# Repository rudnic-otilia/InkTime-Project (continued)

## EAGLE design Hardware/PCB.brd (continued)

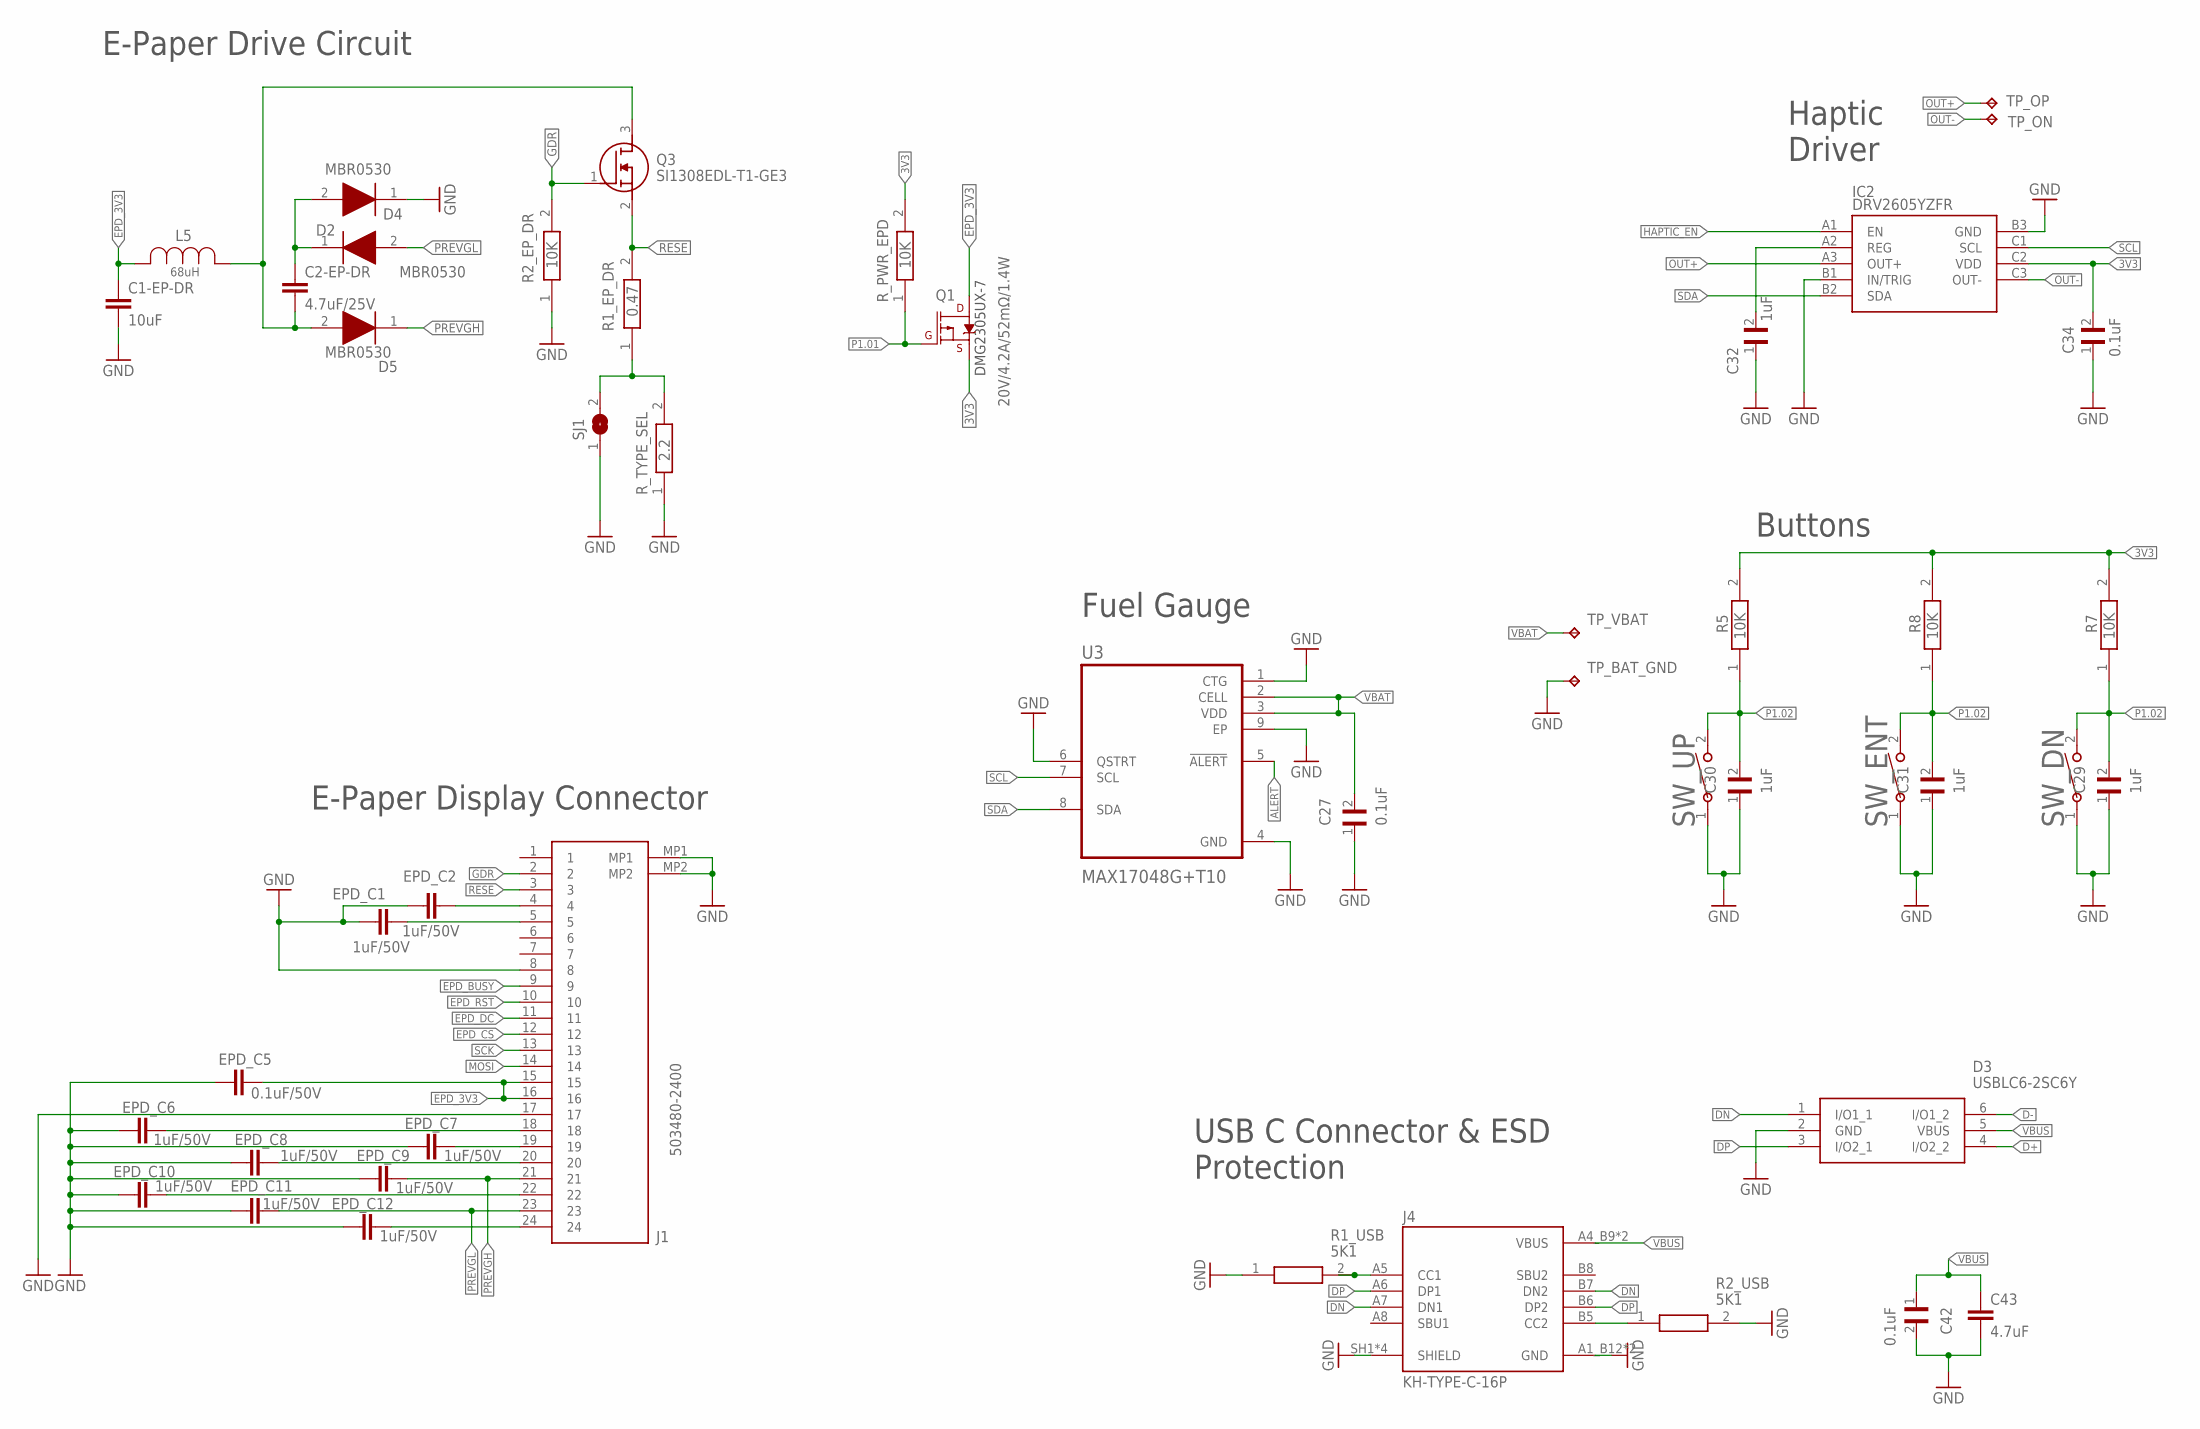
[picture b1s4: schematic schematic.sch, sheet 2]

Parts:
C1-EP-DR: 10uF; NORDIC_NRF_3_RESC0402_L
C2-EP-DR: 4.7uF/25V; NORDIC_NRF_3_RESC0402_L
C27, C34: 0.1uF; GRM011R60J152KE01L_2_CAPC0201X13N
C29, C30, C31: 1uF; GRM011R60J152KE01L_1_0201
C32: 1uF; GRM011R60J152KE01L_2_CAPC0201X13N
C42: 0.1uF; GRM011R60J152KE01L_1_0201
C43: 4.7uF; PERFECT_0402_0402
D2, D4, D5: MBR0530; ESP32_C6_LIBRARY_5_SOD3716X135N
D3: USBLC6-2SC6Y; ESP32_C6_LIBRARY_3_SOT95P280X145-6N
EPD_C1, EPD_C2, EPD_C6, EPD_C7, EPD_C8, EPD_C9, EPD_C10, EPD_C11, EPD_C12: 1uF/50V; NORDIC_NRF_3_RESC0402_L
EPD_C5: 0.1uF/50V; NORDIC_NRF_3_RESC0402_L
IC2: DRV2605YZFR; DRV2605YZFR_BGA9C50P3X3_144X144X62
J1: 503480-2400; 503480-2400_5034802400
J4: KH-TYPE-C-16P; KH-TYPE-C-16P_KINGHELM_KH-TYPE-C-16P
L5: 68uH; ESP32_C6_LIBRARY_2_IND_4828-WE-TPC_WRE
Q1: 20V/4.2A/52mΩ/1.4W; ESP32_C6_LIBRARY_4_ESP32_C6_LIBRARY_4_ESP32_C6_LIBRARY_4_ES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
Q3: SI1308EDL-T1-GE3; ESP32_C6_LIBRARY_6_SOT65P210X110-3N
R1_EP_DR: 0.47; CPF0201D7K68C1_0201
R1_USB, R2_USB: 5K1; CPF0201D7K68C1_0201
R2_EP_DR, R5, R7, R8: 10K; CPF0201D7K68C1_0201
R_PWR_EPD: 10K; CPF0201D7K68C1_0201
R_TYPE_SEL: 2.2; CPF0201D7K68C1_0201
SJ1: ESP32_C6_LIBRARY_7_JUMPER_SJ
SW_DN: 2025-10-22_07-23-44_LIBRARY_EVP-AKE31ASW_EVP-AKE3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; 2025-10-22_07-23-44_LIBRARY_SW_EVP-AKE31A_PAN
SW_ENT: 2025-10-22_07-23-44_LIBRARY_EVP-AKE31ASW_EVP-AKE3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; 2025-10-22_07-23-44_LIBRARY_SW_EVP-AKE31A_PAN
SW_UP: 2025-10-22_07-23-44_LIBRARY_EVP-AKE31ASW_EVP-AKE3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; 2025-10-22_07-23-44_LIBRARY_SW_EVP-AKE31A_PAN
TP_BAT_GND: HECTOR_WATCH_1_TPTP20R; HECTOR_WATCH_1_TP20R
TP_ON: HECTOR_WATCH_1_TPTP20R; HECTOR_WATCH_1_TP20R
TP_OP: HECTOR_WATCH_1_TPTP20R; HECTOR_WATCH_1_TP20R
TP_VBAT: HECTOR_WATCH_1_TPTP20R; HECTOR_WATCH_1_TP20R
U3: MAX17048G+T10; ESP32_C6_LIBRARY_SON50P200X200X80-9N

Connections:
3V3: C34.2, IC2.C2 (VDD), Q1.2 (S), R5.2, R7.2, R8.2, R_PWR_EPD.2; also elsewhere on the board
ALERT: U3.5 (!ALERT); also elsewhere on the board
D+: D3.4 (I/O2_2); also elsewhere on the board
D-: D3.6 (I/O1_2); also elsewhere on the board
DN: D3.1 (I/O1_1), J4.A7 (DN1), J4.B7 (DN2)
DP: D3.3 (I/O2_1), J4.A6 (DP1), J4.B6 (DP2)
EPD_3V3: C1-EP-DR.1, EPD_C5.2, J1.15, J1.16, L5.2, Q1.3 (D)
EPD_BUSY: J1.9; also elsewhere on the board
EPD_CS: J1.12; also elsewhere on the board
EPD_DC: J1.11; also elsewhere on the board
EPD_RST: J1.10; also elsewhere on the board
GDR: J1.2, Q3.1 (G), R2_EP_DR.2
GND: C1-EP-DR.2, C27.1, C29.1, C30.1, C31.1, C32.1, C34.1, C42.2, C43.2, D3.2 (GND), D4.1 (K), EPD_C1.1, EPD_C2.1, EPD_C5.1, EPD_C6.1, EPD_C7.1, EPD_C8.1, EPD_C9.1, EPD_C10.1, EPD_C11.1, EPD_C12.1, IC2.B1 (IN/TRIG), IC2.B3 (GND), J1.8, J1.17, J1.MP1, J1.MP2, J4.A1_B12 (GND), J4.A12_B1 (GND), J4.SH1 (SHIELD), J4.SH2 (SHIELD), J4.SH3 (SHIELD), J4.SH4 (SHIELD), R1_USB.1, R2_EP_DR.1, R2_USB.2, R_TYPE_SEL.1, SJ1.1, SW_DN.1, SW_ENT.1, SW_UP.1, TP_BAT_GND.TP, U3.1 (CTG), U3.4 (GND), U3.6 (QSTRT), U3.9 (EP); also elsewhere on the board
HAPTIC_EN: IC2.A1 (EN); also elsewhere on the board
MOSI: J1.14; also elsewhere on the board
unnamed: C2-EP-DR.2, D5.2 (A), L5.1, Q3.3 (D)
unnamed: C2-EP-DR.1, D2.1 (K), D4.2 (A)
unnamed: R1_EP_DR.1, R_TYPE_SEL.2, SJ1.2
unnamed: EPD_C2.2, J1.4
unnamed: EPD_C7.2, J1.19
unnamed: EPD_C1.2, J1.5
unnamed: C32.2, IC2.A2 (REG)
unnamed: EPD_C12.2, J1.24
unnamed: J4.B5 (CC2), R2_USB.1
unnamed: EPD_C8.2, J1.20
unnamed: EPD_C10.2, J1.22
unnamed: EPD_C6.2, J1.18
unnamed: J4.A5 (CC1), R1_USB.2
OUT+: IC2.A3 (OUT+), TP_OP.TP
OUT-: IC2.C3 (OUT-), TP_ON.TP
P1.01: Q1.1 (G), R_PWR_EPD.1; also elsewhere on the board
P1.02: C29.2, C30.2, C31.2, R5.1, R7.1, R8.1, SW_DN.2, SW_ENT.2, SW_UP.2; also elsewhere on the board
PREVGH: D5.1 (K), EPD_C9.2, J1.21
PREVGL: D2.2 (A), EPD_C11.2, J1.23
RESE: J1.3, Q3.2 (S), R1_EP_DR.2
SCK: J1.13; also elsewhere on the board
SCL: IC2.C1 (SCL), U3.7 (SCL); also elsewhere on the board
SDA: IC2.B2 (SDA), U3.8 (SDA); also elsewhere on the board
VBAT: C27.2, TP_VBAT.TP, U3.2 (CELL), U3.3 (VDD); also elsewhere on the board
VBUS: C42.1, C43.1, D3.5 (VBUS), J4.A4_B9 (VBUS), J4.A9_B4 (VBUS); also elsewhere on the board

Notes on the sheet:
E-Paper Drive Circuit
DMG2305UX-7
E-Paper Display Connector
Haptic Driver
Buttons
USB C Connector & ESD Protection
Fuel Gauge

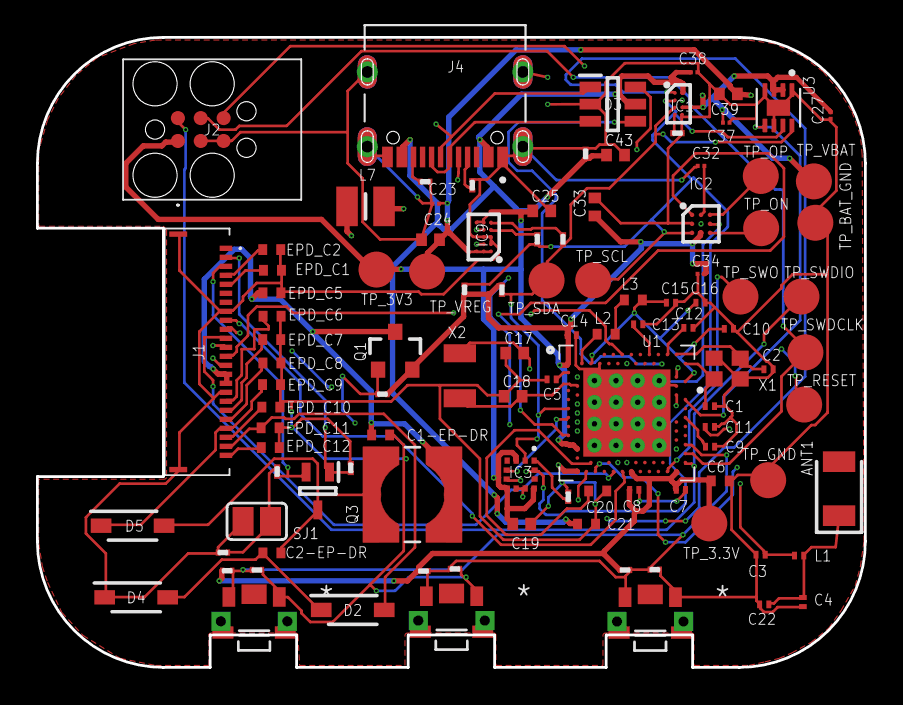
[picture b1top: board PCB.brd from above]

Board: 4 copper layers, 46.0 x 35.0 mm, 105 parts (0 on the bottom side), 69 nets.

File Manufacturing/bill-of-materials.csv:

Reference Designators;Quantity;Description;Package;Value;Manufacturer;Manufacturer Part Number;Vendor;Vendor Part Number;Top/Bottom;
;1;PCB Board;Board;;;;;;;
ANT1;1;Antennas 2.45GHz ANTENNA;2450AT18B100E_ANTC3216X140N;2450AT18B100E;;;;;Top;
C1, C2;2;Generic chip capacitor;NORDIC_NRF_3_RESC0201_L;12pF;;;;;Top;
C1-EP-DR;1;Generic chip capacitor;NORDIC_NRF_3_RESC0402_L;10uF;;;;;Top;
C2-EP-DR;1;Generic chip capacitor;NORDIC_NRF_3_RESC0402_L;4.7uF/25V;;;;;Top;
C3, C4;2;Generic chip capacitor;NORDIC_NRF_3_RESC0201_L;1pF;;;;;Top;
C5, C7, C8, C12;4;Generic chip capacitor;NORDIC_NRF_3_RESC0201_L;100nF;;;;;Top;
C6, C20, C21;3;Generic chip capacitor;NORDIC_NRF_3_RESC0402_L;4.7uF;;;;;Top;
C9;1;Generic chip capacitor;NORDIC_NRF_3_RESC0201_L;820pF;;;;;Top;
C10, C13, C22;3;Generic chip capacitor;NORDIC_NRF_3_RESC0201_L;N.C.;;;;;Top;
C11;1;Generic chip capacitor;NORDIC_NRF_3_RESC0201_L;100pF;;;;;Top;
C14;1;Generic chip capacitor;NORDIC_NRF_3_RESC0201_L;4.7uF;;;;;Top;
C15;1;Generic chip capacitor;NORDIC_NRF_3_RESC0201_L;1.0uF;;;;;Top;
C16;1;Generic chip capacitor;NORDIC_NRF_3_RESC0201_L;47nF;;;;;Top;
C17, C18;2;0402 (1005 Metric);PERFECT_0402_0402;12pF;;;;;Top;
C19;1;0402 (1005 Metric);PERFECT_0402_0402;100nF;;;;;Top;
C23, C27, C34;3;Check availability;CAPC0201X13N;0.1uF;;;;;Top;
C24, C39;2;0402 (1005 Metric);PERFECT_0402_0402;10uF;;;;;Top;
C25, C33;2;0402 (1005 Metric);PERFECT_0402_0402;22uF;;;;;Top;
C29, C30, C31;3;Check availability;GRM011R60J152KE01L_1_0201;1uF;;;;;Top;
C32, C37, C38;3;Check availability;CAPC0201X13N;1uF;;;;;Top;
C42;1;Check availability;GRM011R60J152KE01L_1_0201;0.1uF;;;;;Top;
C43;1;0402 (1005 Metric);PERFECT_0402_0402;4.7uF;;;;;Top;
D2, D4, D5;3;ON SEMICONDUCTOR - MBR0530 - DIODE, SCHOTTKY, 0.5A, 30V, SOD-123;SOD3716X135N;MBR0530;;;;;Top;
D3;1;Low Cap. ESD Protection Auto SOT-23-6 STMicroelectronics USBLC6-2SC6Y, Dual Uni-Directional TVS Diode Array, 6-Pin SOT-23;SOT95P280X145-6N;USBLC6-2SC6Y;;;;;Top;
EPD_C1, EPD_C2, EPD_C6, EPD_C7, EPD_C8, EPD_C9, EPD_C10, EPD_C11, EPD_C12;9;Generic chip capacitor;NORDIC_NRF_3_RESC0402_L;1uF/50V;;;;;Top;
EPD_C5;1;Generic chip capacitor;NORDIC_NRF_3_RESC0402_L;0.1uF/50V;;;;;Top;
IC1;1;Charger IC Lithium Ion/Polymer, Lithium Iron Phosphate 8-DSBGA (1.6x1.1);BQ25180YBGR_BGA8C40P2X4_100X155X50;BQ25180YBGR;;;;;Top;
IC2;1;Haptic Driver for ERM/LRA with Built-In Library and Smart Loop Architecture;DRV2605YZFR_BGA9C50P3X3_144X144X62;DRV2605YZFR;;;;;Top;
IC3;1;Accelerometers Triaxial low-g 12bit Acceleration Sensor;BMA423_BMA423;BMA423;;;;;Top;
IC9;1;Buck-Boost Regulator Positive Output Step-Up/Step-Down I2C DC-DC Controller IC 15-WL-CSP (BSC) (1.4x2.3);RT6160AWSC_BGA15C40P3X5_140X230X60;RT6160AWSC;;;;;Top;
J1;1;FFC & FPC Connectors 0.5mm FPC RA SMT Dual Contact 24Ckt;503480-2400_5034802400;503480-2400;;;;;Top;
J2;1;CABLE ADAPTER 6 POS;TC2030-IDC_TC2030IDC;TC2030-IDC;;;;;Top;
J4;1;Check availability;KINGHELM_KH-TYPE-C-16P;KH-TYPE-C-16P;;;;;Top;
L1;1;Generic chip inductor;NORDIC_NRF_2_RESC0201_L;3.9nH;;;;;Top;
L2;1;Generic chip inductor;NORDIC_NRF_2_RESC0402_L;10uH;;;;;Top;
L3;1;Generic chip inductor;NORDIC_NRF_2_RESC0402_L;15nH;;;;;Top;
L5;1;;ESP32_C6_LIBRARY_2_IND_4828-WE-TPC_WRE;68uH;;;;;Top;
L7;1;SMD / SMT Inductors (Coils), L=0.47?H, L x W x T :;MLP2016SR47MT0S1_INDC2016X100N;FTC252012SR47MBCA;;;;;Top;
Q1;1;P-channel MOSFETs;ESP32_WROVER_SPARKFUN-DISCRETESEMI_SOT23-3;20V/4.2A/52mΩ/1.4W;;;;;Top;
Q3;1;MOSFET N-Ch 30V 1.5A TrenchFET SC70 Vishay Si1308EDL-T1-GE3 N-channel MOSFET Transistor, 1.5 A, 30 V, 3-Pin SC-70;SOT65P210X110-3N;SI1308EDL-T1-GE3;;;;;Top;
R_PWR_EPD, R2_EP_DR, R5, R7, R8, R9;6;7.68k 0201 Thin Film Surface Mount Fixed Resistor +/-0.5% 0.031W CPF0201D7K68C1;CPF0201D7K68C1_0201;10K;;;;;Top;
R_TYPE_SEL;1;7.68k 0201 Thin Film Surface Mount Fixed Resistor +/-0.5% 0.031W CPF0201D7K68C1;CPF0201D7K68C1_0201;2.2;;;;;Top;
R1_EP_DR;1;7.68k 0201 Thin Film Surface Mount Fixed Resistor +/-0.5% 0.031W CPF0201D7K68C1;CPF0201D7K68C1_0201;0.47;;;;;Top;
R1_USB, R2_USB;2;7.68k 0201 Thin Film Surface Mount Fixed Resistor +/-0.5% 0.031W CPF0201D7K68C1;CPF0201D7K68C1_0201;5K1;;;;;Top;
R2, R4;2;7.68k 0201 Thin Film Surface Mount Fixed Resistor +/-0.5% 0.031W CPF0201D7K68C1;R0201;0;;;;;Top;
R3;1;7.68k 0201 Thin Film Surface Mount Fixed Resistor +/-0.5% 0.031W CPF0201D7K68C1;CPF0201D7K68C1_0201;0;;;;;Top;
R17, R18;2;7.68k 0201 Thin Film Surface Mount Fixed Resistor +/-0.5% 0.031W CPF0201D7K68C1;CPF0201D7K68C1_0201;3K3;;;;;Top;
SJ1;1;SMD solder JUMPER;JUMPER_SJ;;;;;;Top;
SW_DN, SW_ENT, SW_UP;3;;SW_EVP-AKE31A_PAN;2025-10-22_07-23-44_LIBRARY_EVP-AKE31ASW_EVP-AKE31A_PAN;;;;;Top;
TP_3.3V, TP_3V3, TP_BAT_GND, TP_GND, TP_ON, TP_OP, TP_RESET, TP_SCL, TP_SDA, TP_SWDCLK, TP_SWDIO, TP_SWO, TP_VBAT, TP_VREG;14;Test pad;HECTOR_WATCH_1_TP20R;HECTOR_WATCH_1_TPTP20R;;;;;Top;
U1;1;nRF52840;NORDIC_NRF_4_AQFN50P700X700X85_HS-74N;NRF52840_QF;;;;;Top;
U3;1;Check availability;SON50P200X200X80-9N;MAX17048G+T10;;;;;Top;
X1;1;;NORDIC_NRF_BT-XTAL_2016_N;32MHZ;;;;;Top;
X2;1;;NORDIC_NRF_1_XTAL_3215_N;32.768kHz;;;;;Top;

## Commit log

2026-04-10 Add GNU GPL v3 license
    Added the GNU General Public License version 3 to the project.
2026-04-10 Add PCB
2026-04-10 Add initial README.md with project details
2026-04-18 Revise BOM with detailed components and notes
    Updated the Bill of Materials section to include detailed components, descriptions, packages, quantities, and links for each item. Added passive components and notes regarding assembly and budgeting.
2026-04-18 Revise README for hardware and design details
    Updated README.md to reflect hardware descriptions, component references, and design decisions.
2026-04-18 update project files and rename hardware assets
